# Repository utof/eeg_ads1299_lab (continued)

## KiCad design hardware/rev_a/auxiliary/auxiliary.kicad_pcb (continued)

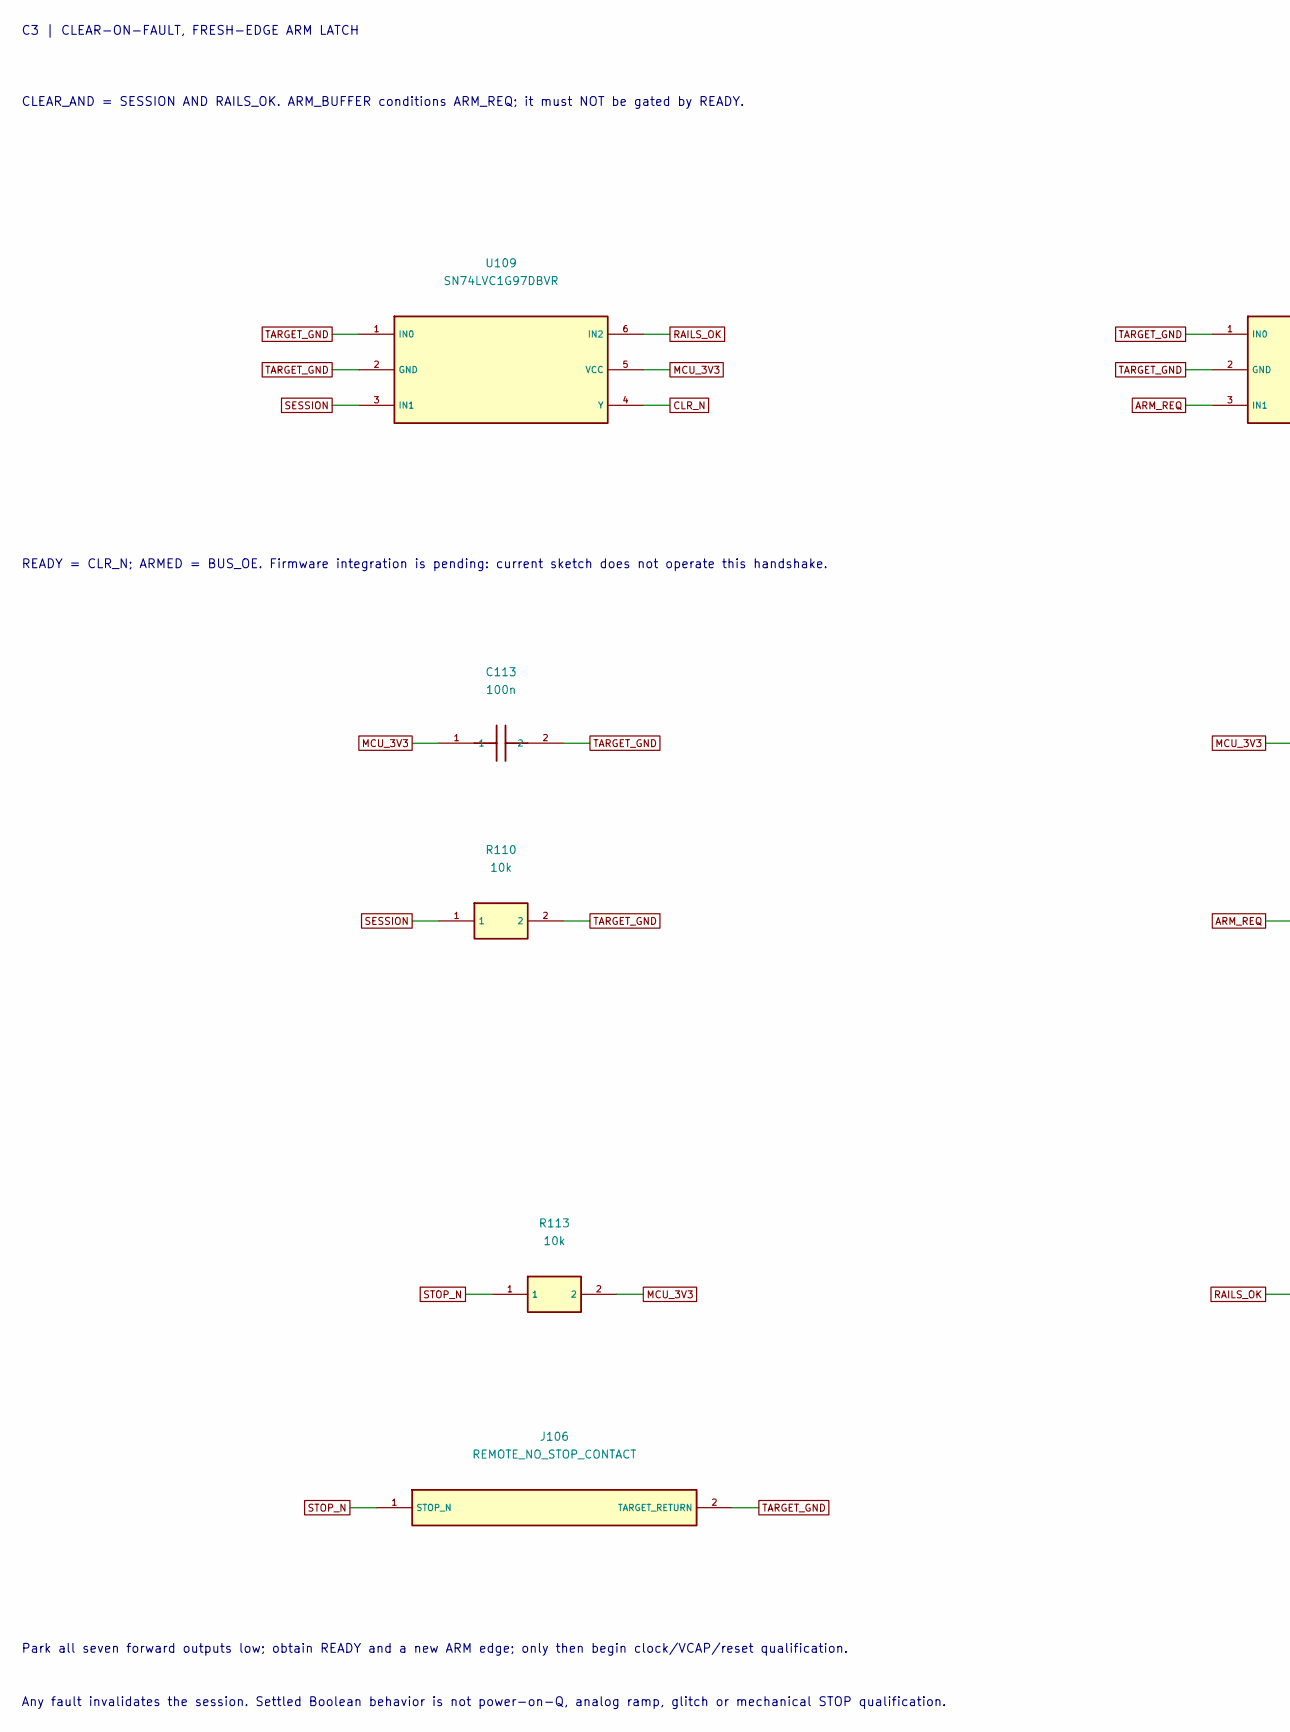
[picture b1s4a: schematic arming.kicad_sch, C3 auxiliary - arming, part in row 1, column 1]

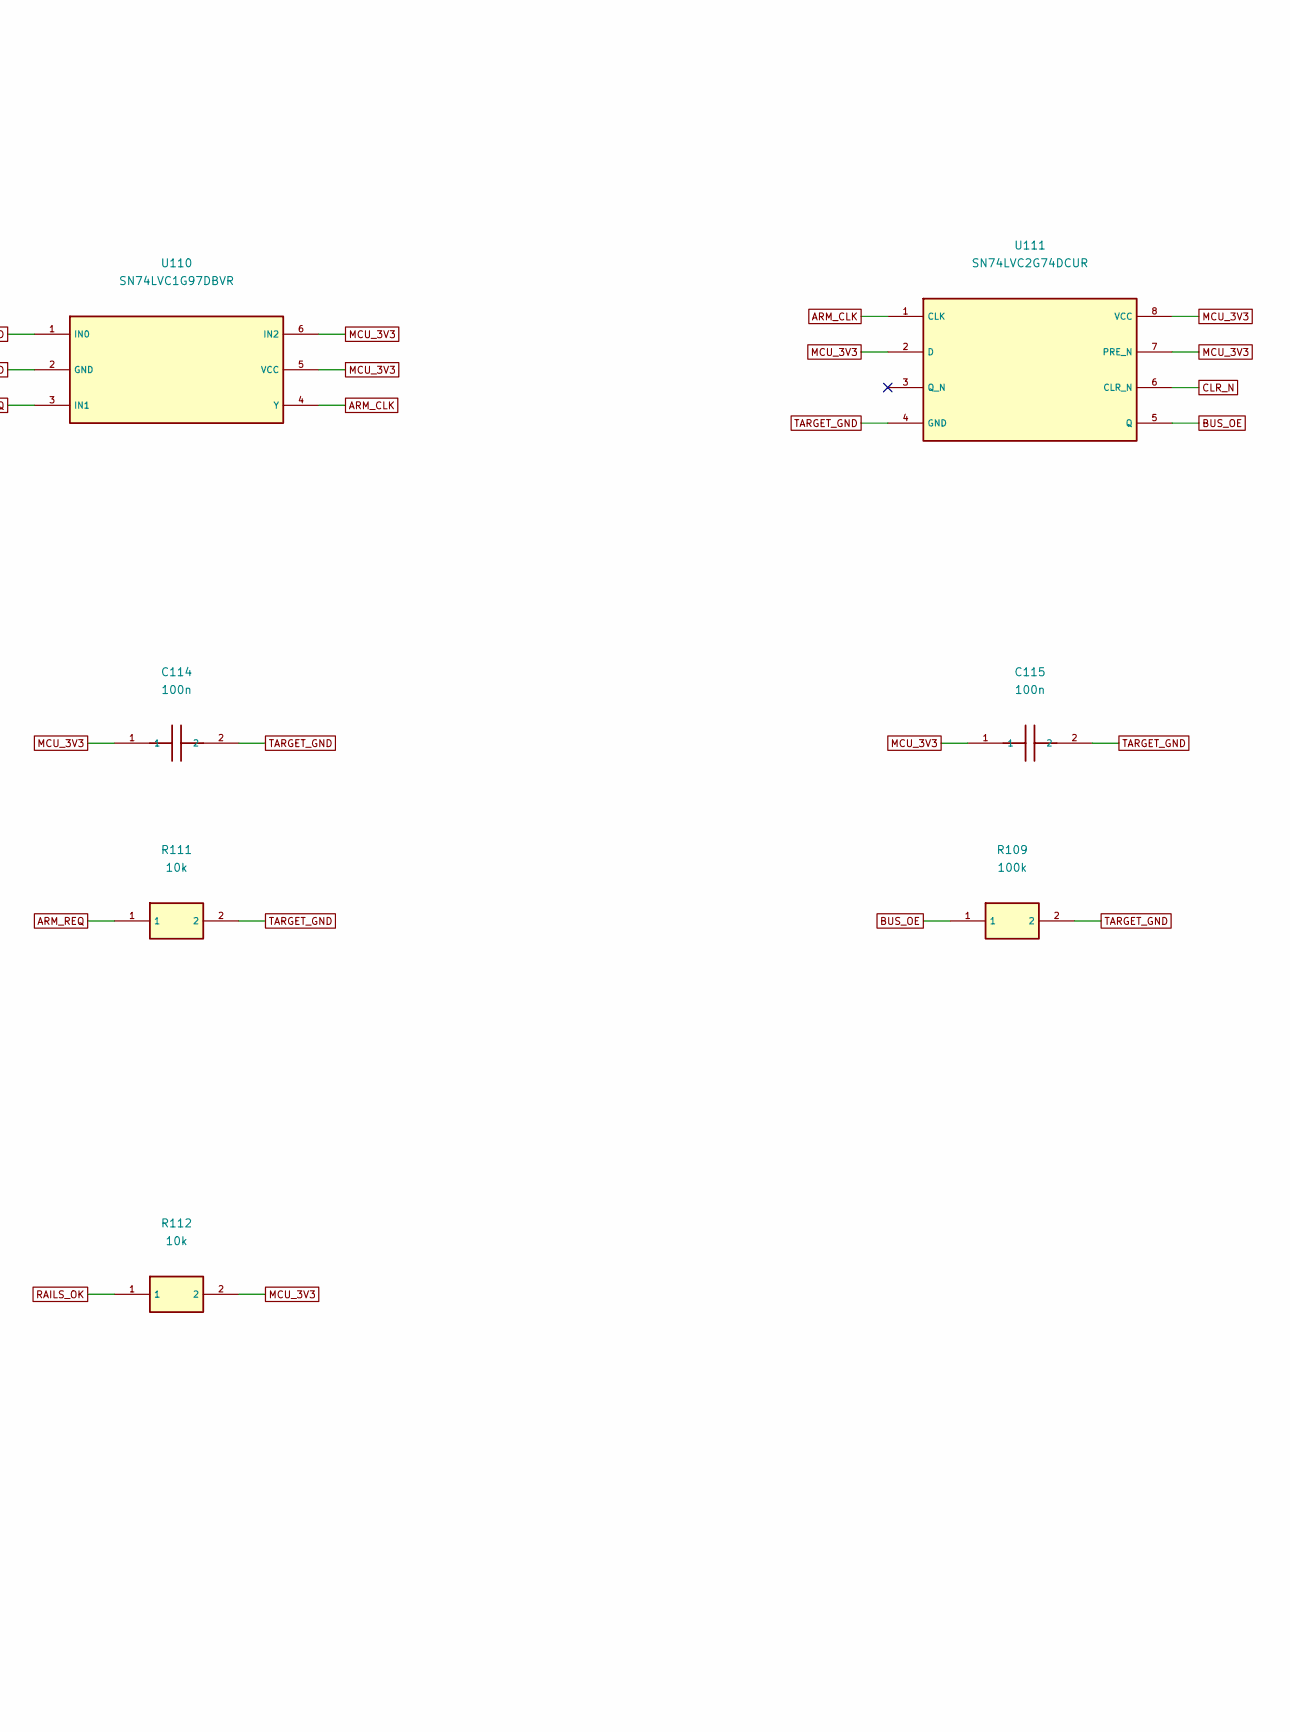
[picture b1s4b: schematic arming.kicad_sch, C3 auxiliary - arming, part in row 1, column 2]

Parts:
C113, C114, C115: 100n; C_0603_1608Metric; MPN C0603C104K5RACTU
J106: REMOTE_NO_STOP_CONTACT; SolderTails_2; MPN PCB_LANDINGS_ONLY
R109: 100k; R_0603_1608Metric; MPN RC0603FR-07100KL
R110, R111, R112, R113: 10k; R_0603_1608Metric; MPN RC0603FR-0710KL
U109, U110: SN74LVC1G97DBVR; SOT-23-6; MPN SN74LVC1G97DBVR
U111: SN74LVC2G74DCUR; VSSOP-8_2.3x2mm_P0.5mm; MPN SN74LVC2G74DCUR

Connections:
ARM_CLK: U110.4 (Y), U111.1 (CLK)
ARM_REQ: R111.1, U110.3 (IN1); also elsewhere on the board
BUS_OE: R109.1, U111.5 (Q); also elsewhere on the board
CLR_N: U109.4 (Y), U111.6 (CLR_N); also elsewhere on the board
MCU_3V3: C113.1, C114.1, C115.1, R112.2, R113.2, U109.5 (VCC), U110.5 (VCC), U110.6 (IN2), U111.2 (D), U111.7 (PRE_N), U111.8 (VCC); also elsewhere on the board
RAILS_OK: R112.1, U109.6 (IN2); also elsewhere on the board
SESSION: R110.1, U109.3 (IN1); also elsewhere on the board
STOP_N: J106.1 (STOP_N), R113.1; also elsewhere on the board
TARGET_GND: C113.2, C114.2, C115.2, J106.2 (TARGET_RETURN), R109.2, R110.2, R111.2, U109.1 (IN0), U109.2 (GND), U110.1 (IN0), U110.2 (GND), U111.4 (GND); also elsewhere on the board

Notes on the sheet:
C3 | CLEAR-ON-FAULT, FRESH-EDGE ARM LATCH
CLEAR_AND = SESSION AND RAILS_OK. ARM_BUFFER conditions ARM_REQ; it must NOT be gated by READY.
READY = CLR_N; ARMED = BUS_OE. Firmware integration is pending: current sketch does not operate this handshake.
Park all seven forward outputs low; obtain READY and a new ARM edge; only then begin clock/VCAP/reset qualification.
Any fault invalidates the session. Settled Boolean behavior is not power-on-Q, analog ramp, glitch or mechanical STOP qualification.

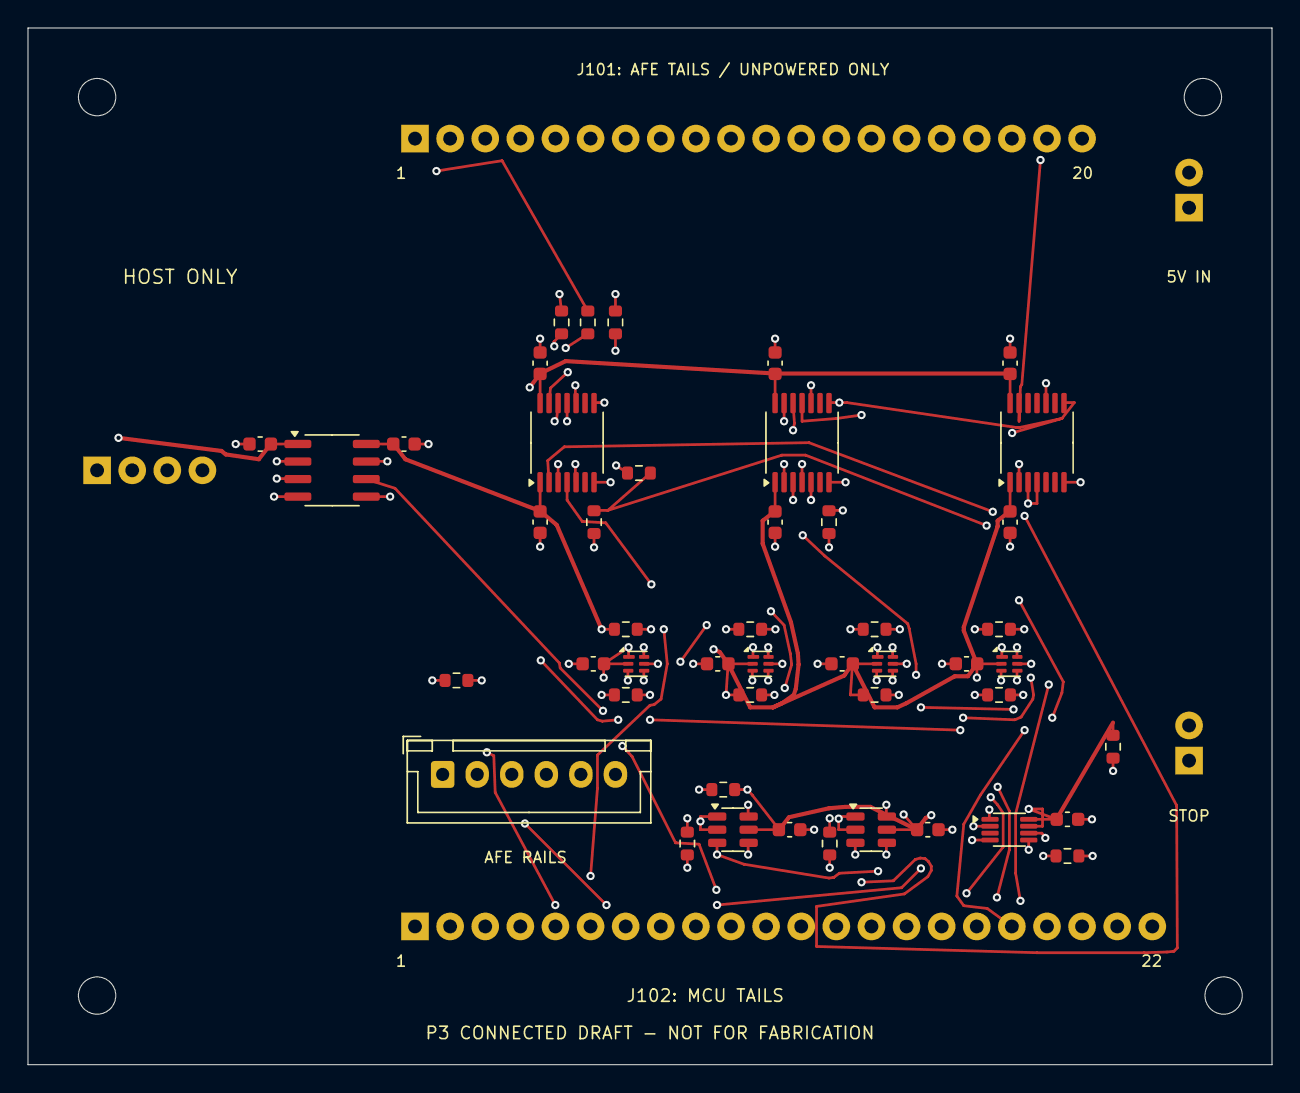
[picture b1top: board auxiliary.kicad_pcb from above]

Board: 4 copper layers, 90.0 x 75.0 mm, 56 parts (0 on the bottom side), 45 nets.

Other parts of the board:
H1, H2, H3, H4: M2.5_CLEARANCE_ONLY; MountingHole_2.7mm_M2.5

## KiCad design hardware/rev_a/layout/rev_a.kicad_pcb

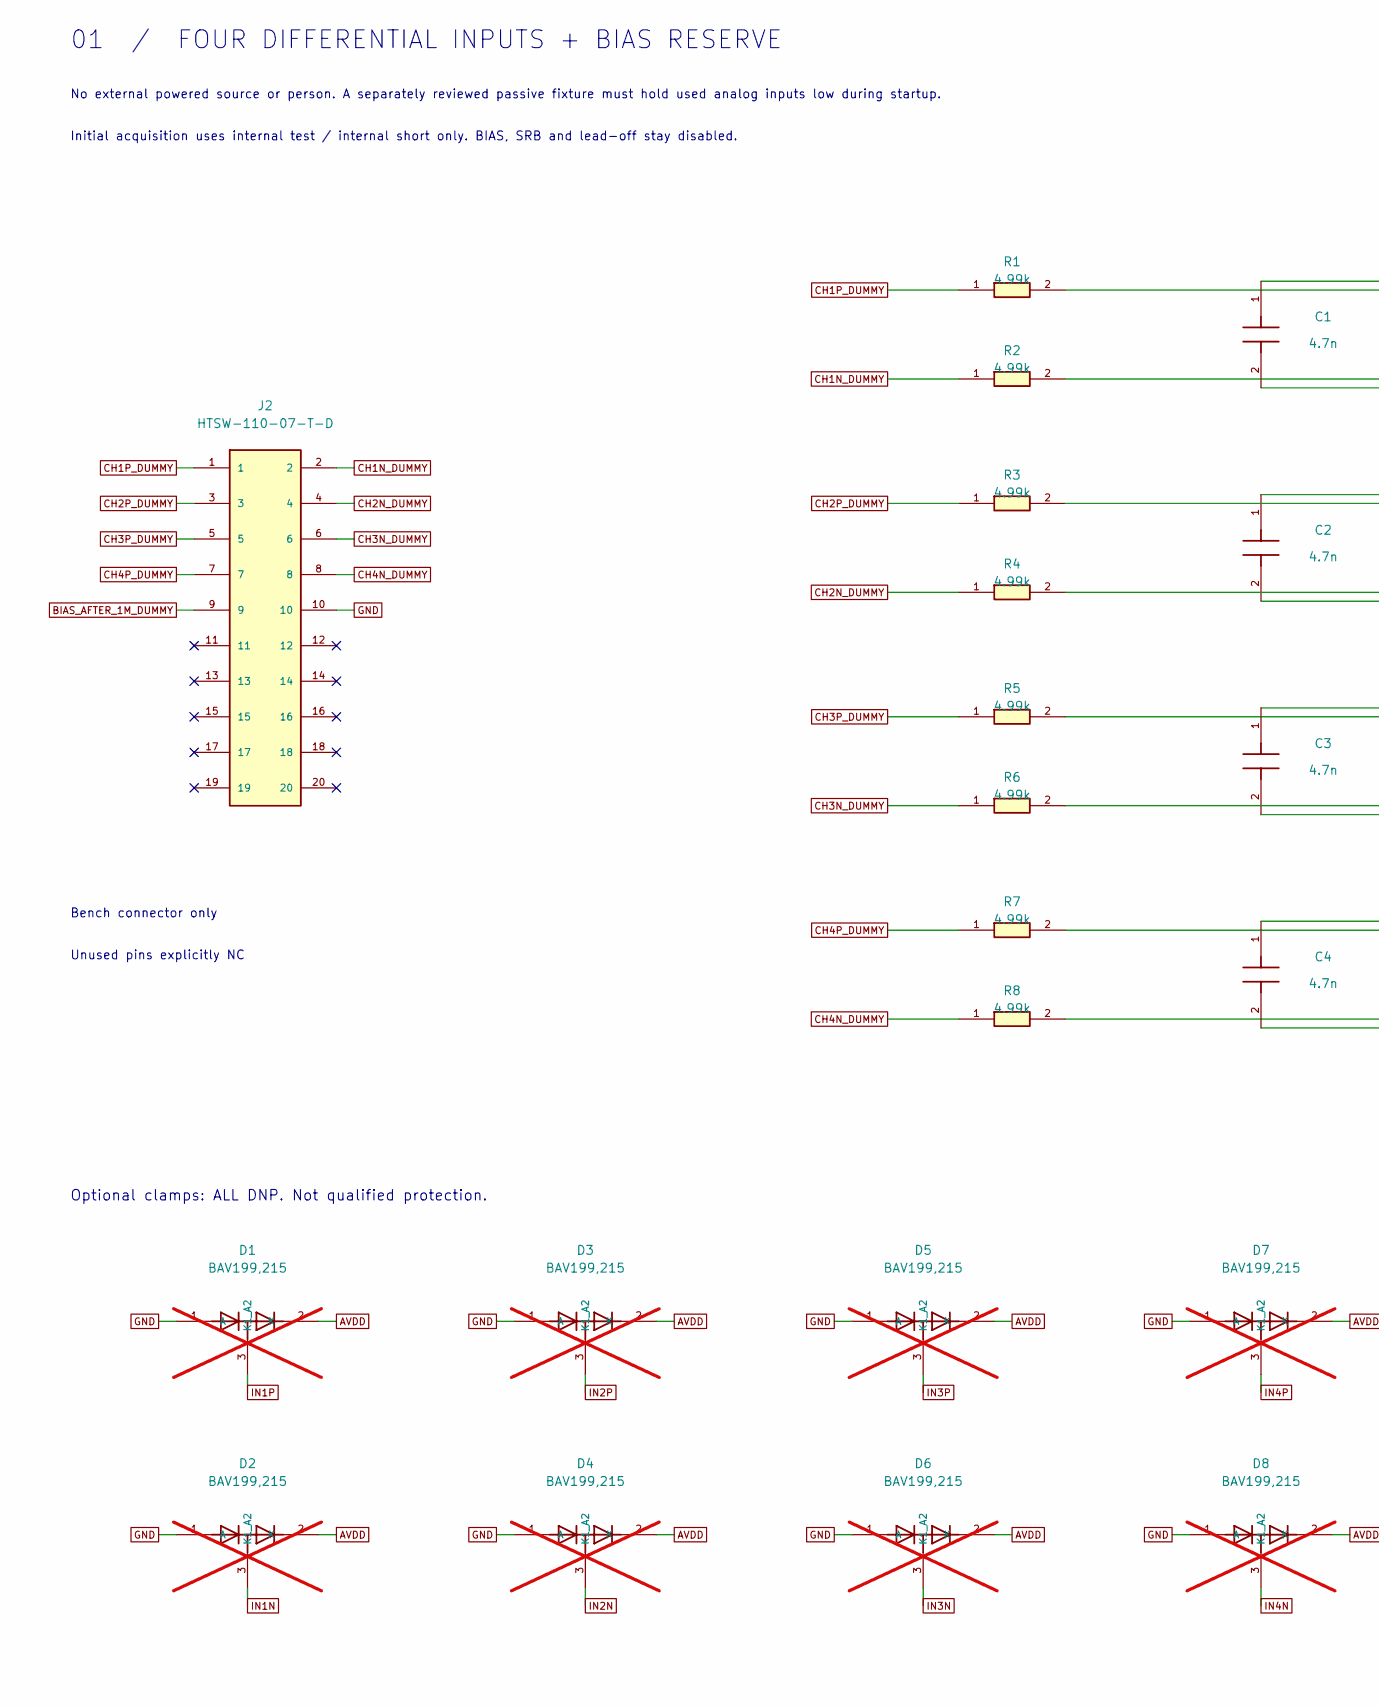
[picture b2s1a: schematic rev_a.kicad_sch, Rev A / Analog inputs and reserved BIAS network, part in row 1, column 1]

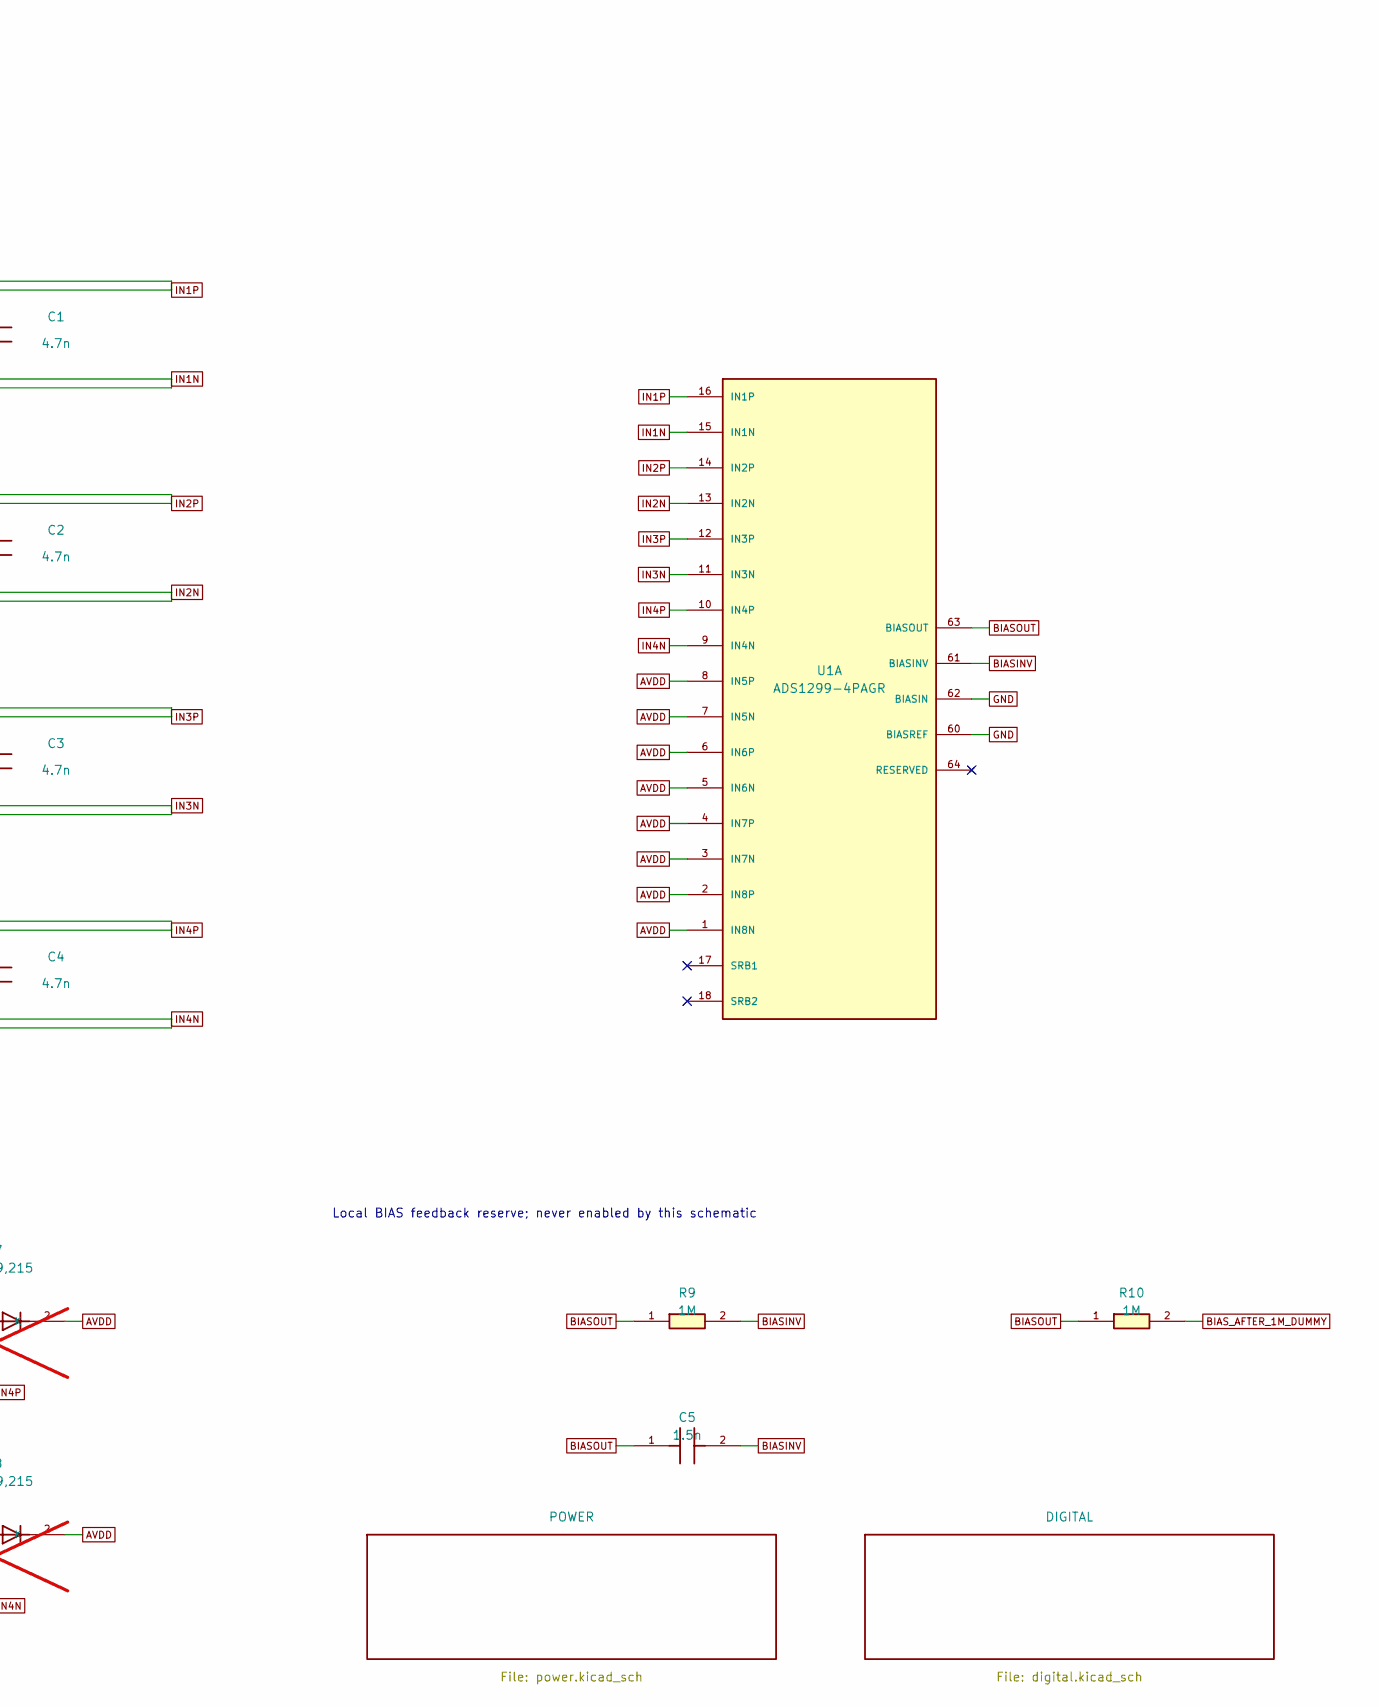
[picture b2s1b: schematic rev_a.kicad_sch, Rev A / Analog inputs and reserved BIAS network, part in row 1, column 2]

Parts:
C1, C2, C3, C4: 4.7n; C_0603_1608Metric; Tolerance 0.05; MPN GRM1885C1H472JA01D
C5: 1.5n; C_0603_1608Metric; Tolerance 0.05; MPN GRM1885C1H152JA01D
D1, D2, D3, D4, D5, D6, D7, D8: BAV199,215; SOT-23; MPN BAV199,215; not fitted
J2: HTSW-110-07-T-D; PinHeader_2x10_P2.54mm_Vertical; MPN HTSW-110-07-T-D
R1, R2, R3, R4, R5, R6, R7, R8: 4.99k; R_0603_1608Metric; Tolerance 0.01; MPN RC0603FR-074K99L
R9, R10: 1M; R_0603_1608Metric; Tolerance 0.01; MPN RC0603FR-071ML
U1: ADS1299-4PAGR; TQFP-64_10x10mm_P0.5mm; MPN ADS1299-4PAGR

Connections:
AVDD: D1.2 (K), D2.2 (K), D3.2 (K), D4.2 (K), D5.2 (K), D6.2 (K), D7.2 (K), D8.2 (K), U1.1 (IN8N), U1.2 (IN8P), U1.3 (IN7N), U1.4 (IN7P), U1.5 (IN6N), U1.6 (IN6P), U1.7 (IN5N), U1.8 (IN5P); also elsewhere on the board
BIASINV: C5.2, R9.2, U1.61 (BIASINV)
BIASOUT: C5.1, R9.1, R10.1, U1.63 (BIASOUT)
BIAS_AFTER_1M_DUMMY: J2.9, R10.2
CH1N_DUMMY: J2.2, R2.1
CH1P_DUMMY: J2.1, R1.1
CH2N_DUMMY: J2.4, R4.1
CH2P_DUMMY: J2.3, R3.1
CH3N_DUMMY: J2.6, R6.1
CH3P_DUMMY: J2.5, R5.1
CH4N_DUMMY: J2.8, R8.1
CH4P_DUMMY: J2.7, R7.1
GND: D1.1 (A), D2.1 (A), D3.1 (A), D4.1 (A), D5.1 (A), D6.1 (A), D7.1 (A), D8.1 (A), J2.10, U1.60 (BIASREF), U1.62 (BIASIN); also elsewhere on the board
IN1N: C1.2, D2.3 (K1_A2), R2.2, U1.15 (IN1N)
IN1P: C1.1, D1.3 (K1_A2), R1.2, U1.16 (IN1P)
IN2N: C2.2, D4.3 (K1_A2), R4.2, U1.13 (IN2N)
IN2P: C2.1, D3.3 (K1_A2), R3.2, U1.14 (IN2P)
IN3N: C3.2, D6.3 (K1_A2), R6.2, U1.11 (IN3N)
IN3P: C3.1, D5.3 (K1_A2), R5.2, U1.12 (IN3P)
IN4N: C4.2, D8.3 (K1_A2), R8.2, U1.9 (IN4N)
IN4P: C4.1, D7.3 (K1_A2), R7.2, U1.10 (IN4P)

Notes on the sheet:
01 / FOUR DIFFERENTIAL INPUTS + BIAS RESERVE
No external powered source or person. A separately reviewed passive fixture must hold used analog inputs low during startup.
Initial acquisition uses internal test / internal short only. BIAS, SRB and lead-off stay disabled.
Bench connector only
Unused pins explicitly NC
Local BIAS feedback reserve; never enabled by this schematic
Optional clamps: ALL DNP. Not qualified protection.

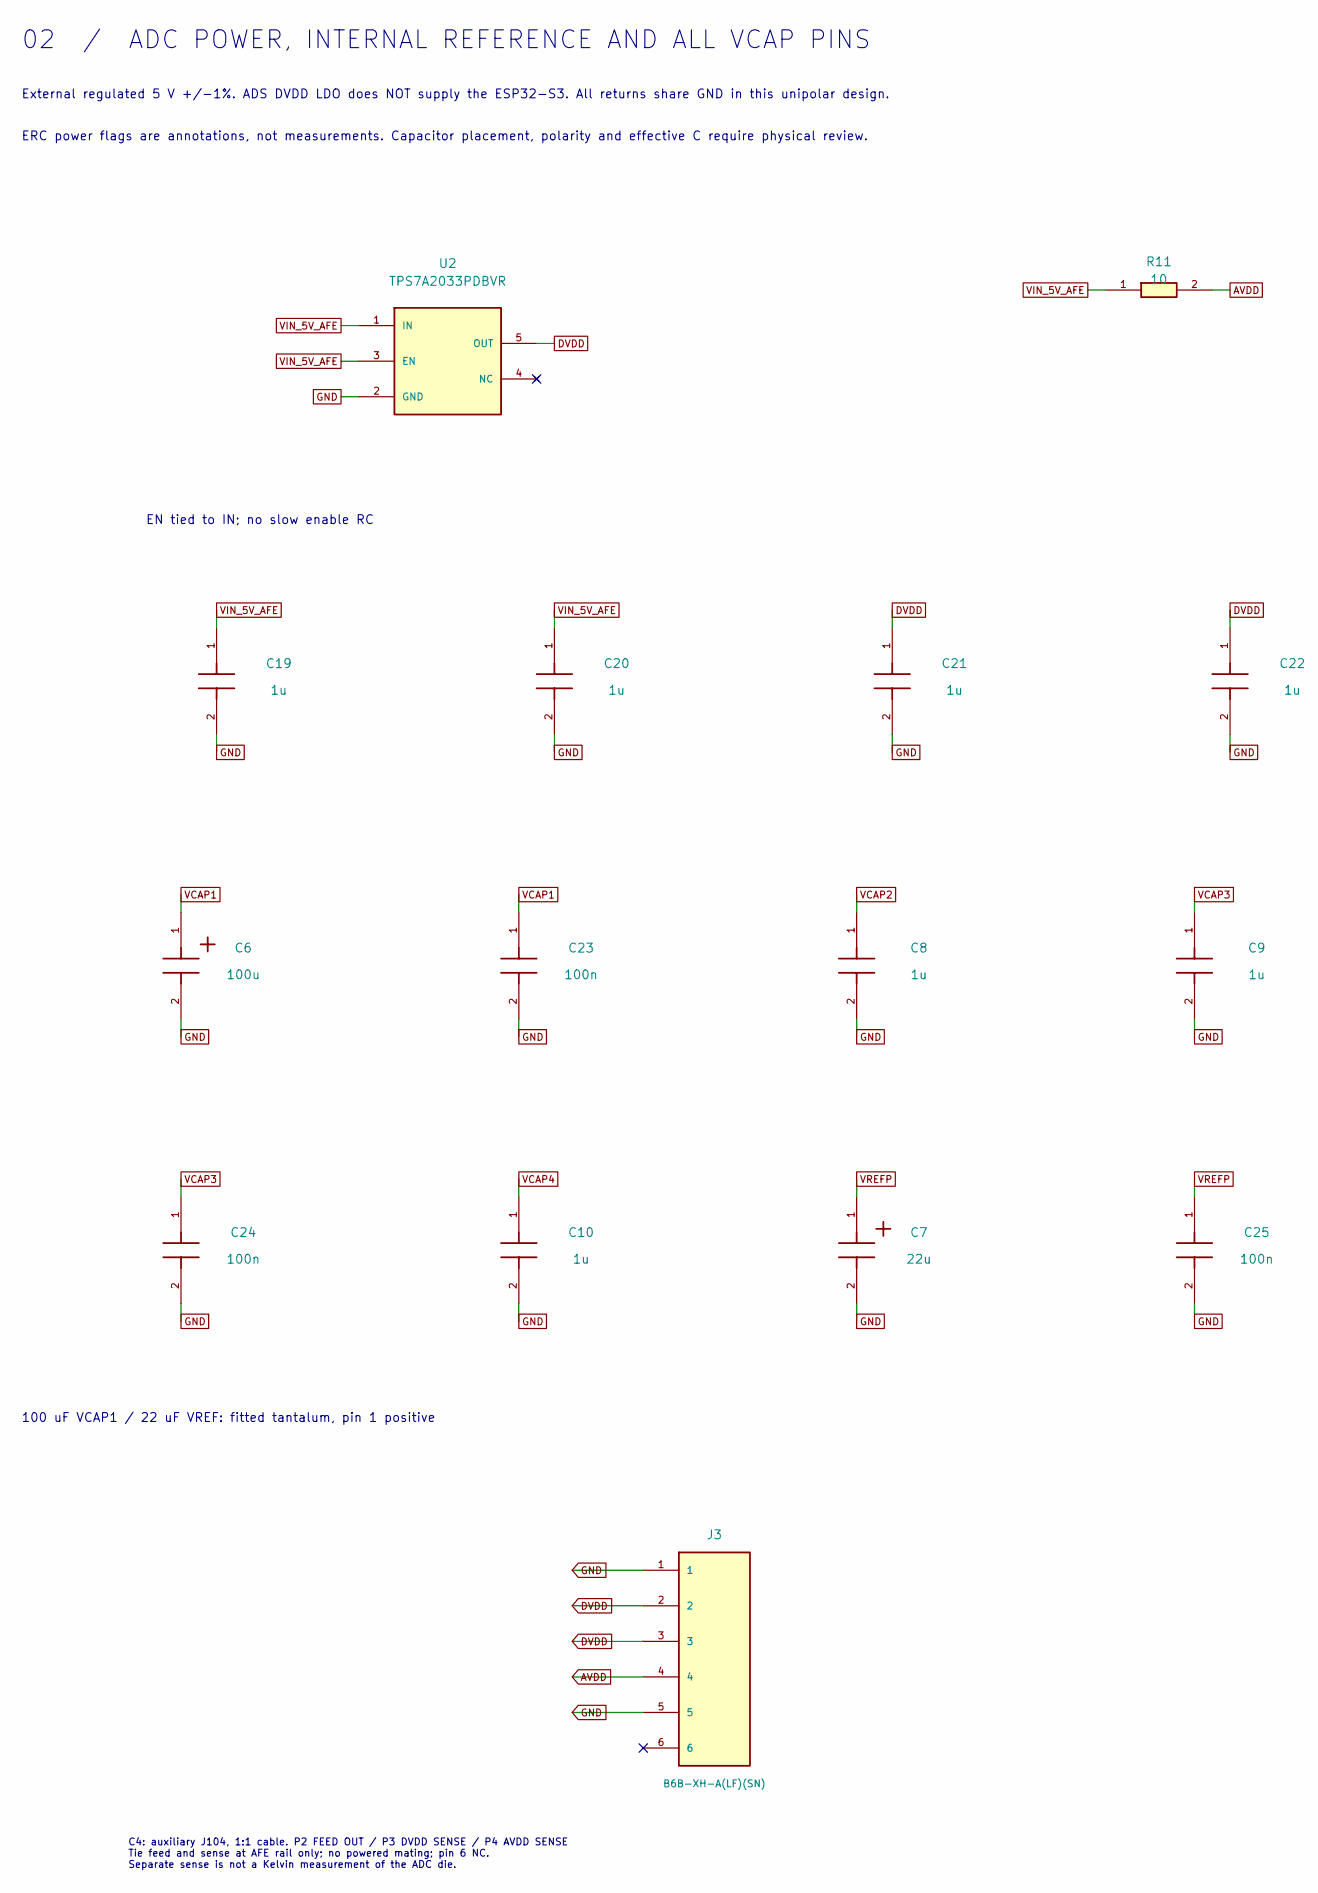
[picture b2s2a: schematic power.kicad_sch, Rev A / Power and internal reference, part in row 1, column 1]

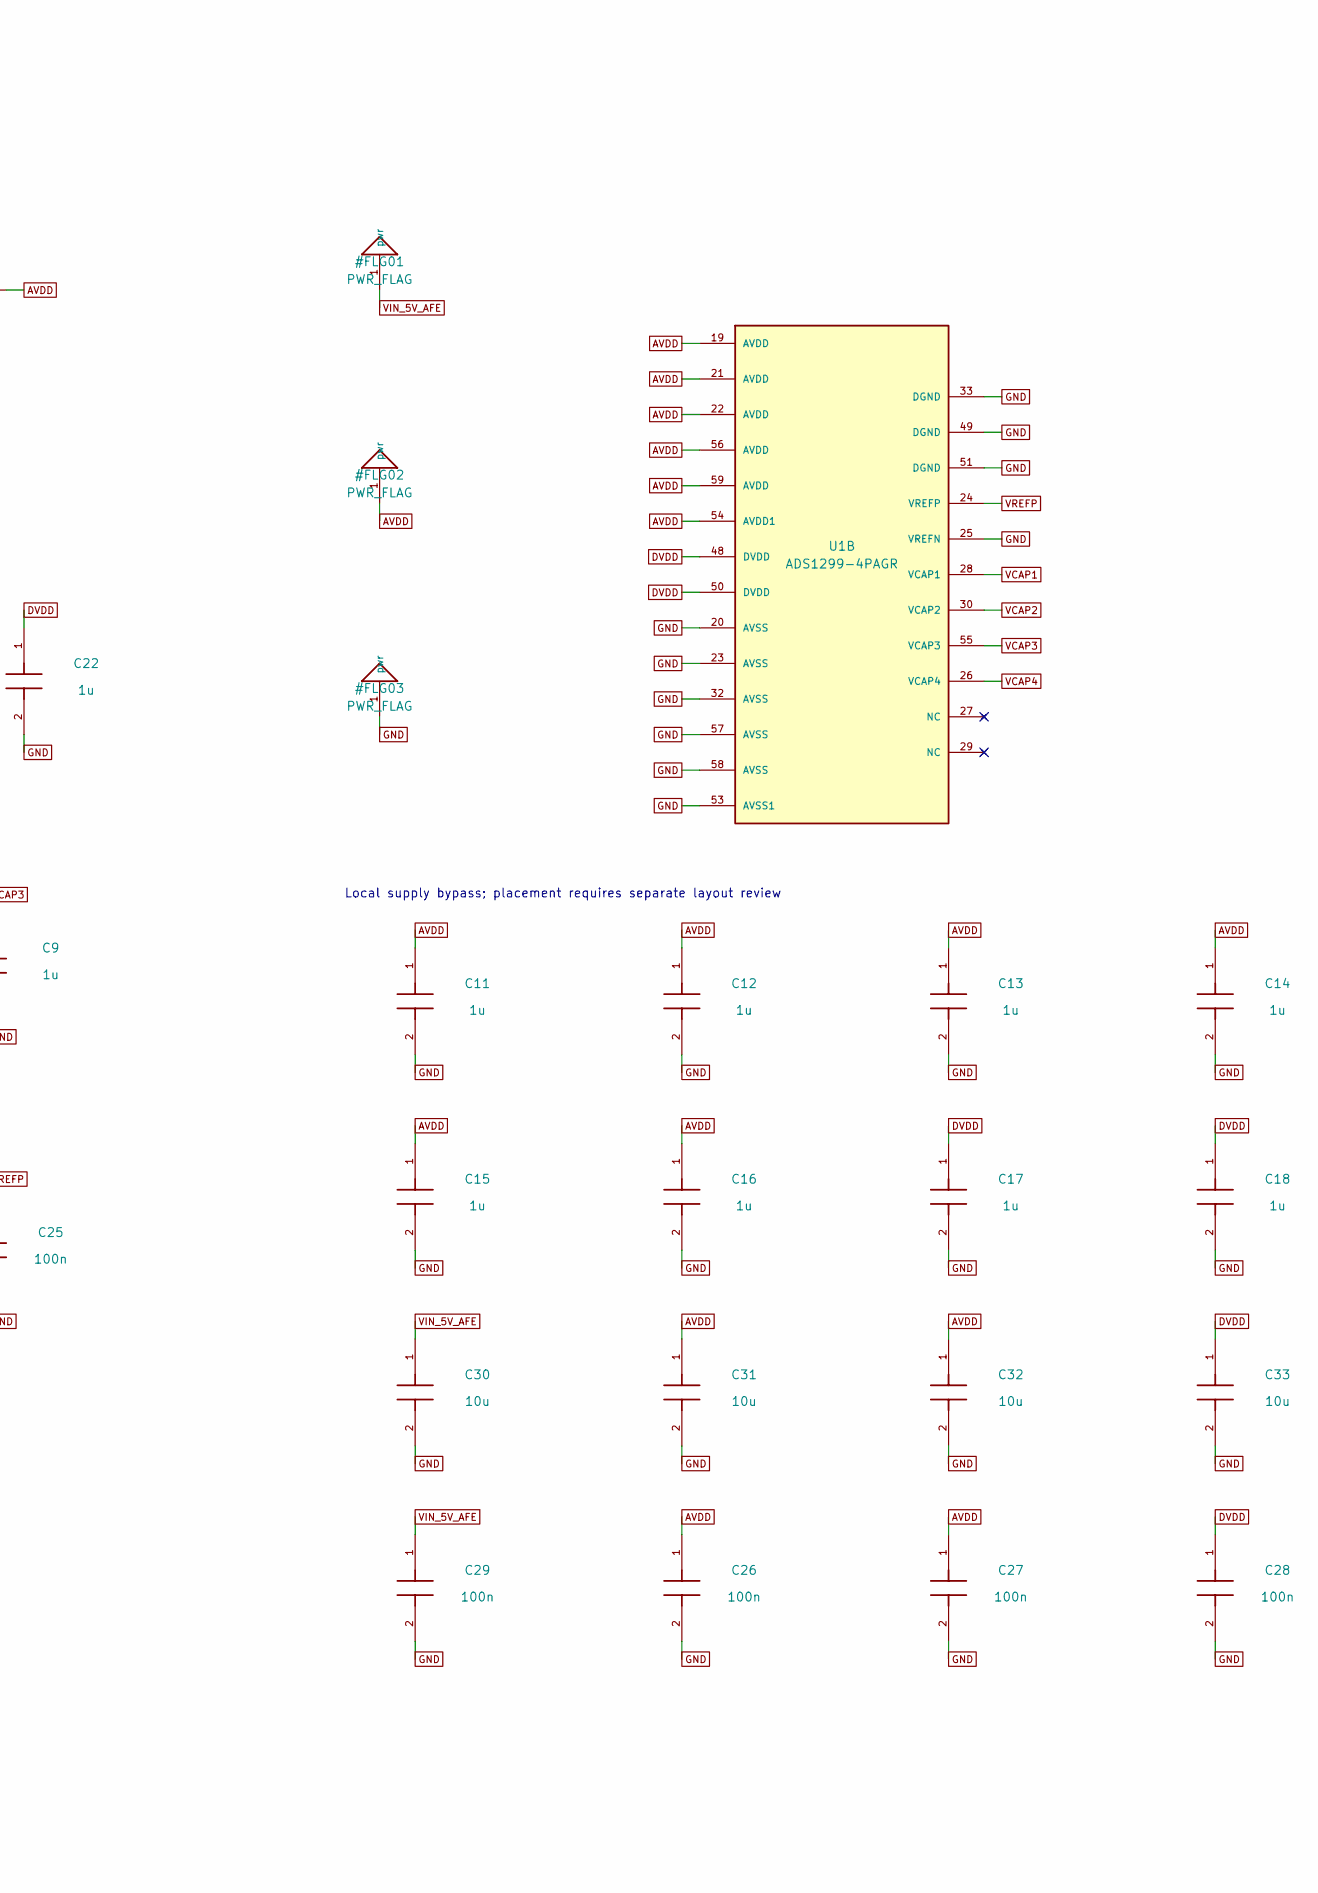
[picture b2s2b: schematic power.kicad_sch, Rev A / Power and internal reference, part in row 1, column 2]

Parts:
C6: 100u; T491D_7343_DensityB; Tolerance 0.1; MPN T491D107K016AT
C7: 22u; T491B_3528_DensityB; Tolerance 0.1; MPN T491B226K016AT
C8, C9, C10, C11, C12, C13, C14, C15, C16, C17, C18, C19, C20, C21, C22: 1u; C_0603_1608Metric; Tolerance 0.1; MPN GRM188R61E105KA12D
C23, C24, C25, C26, C27, C28, C29: 100n; C_0603_1608Metric; Tolerance 0.1; MPN GRM188R71H104KA93D
C30, C31, C32, C33: 10u; C_0805_2012Metric; Tolerance 0.1; MPN GRM219R61A106KE44D
J3: B6B-XH-A(LF)(SN); JST_XH_B6B-XH-A_1x06_P2.50mm_Vertical; MPN B6B-XH-A(LF)(SN)
R11: 10; R_0603_1608Metric; Tolerance 0.01; MPN RC0603FR-0710RL
U1: ADS1299-4PAGR; TQFP-64_10x10mm_P0.5mm; MPN ADS1299-4PAGR
U2: TPS7A2033PDBVR; SOT-23-5; MPN TPS7A2033PDBVR

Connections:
AVDD: C11.1, C12.1, C13.1, C14.1, C15.1, C16.1, C26.1, C27.1, C31.1, C32.1, J3.4, R11.2, U1.19 (AVDD), U1.21 (AVDD), U1.22 (AVDD), U1.54 (AVDD1), U1.56 (AVDD), U1.59 (AVDD); also elsewhere on the board
DVDD: C17.1, C18.1, C21.1, C22.1, C28.1, C33.1, J3.2, J3.3, U1.48 (DVDD), U1.50 (DVDD), U2.5 (OUT)
GND: C6.2, C7.2, C8.2, C9.2, C10.2, C11.2, C12.2, C13.2, C14.2, C15.2, C16.2, C17.2, C18.2, C19.2, C20.2, C21.2, C22.2, C23.2, C24.2, C25.2, C26.2, C27.2, C28.2, C29.2, C30.2, C31.2, C32.2, C33.2, J3.1, J3.5, U1.20 (AVSS), U1.23 (AVSS), U1.25 (VREFN), U1.32 (AVSS), U1.33 (DGND), U1.49 (DGND), U1.51 (DGND), U1.53 (AVSS1), U1.57 (AVSS), U1.58 (AVSS), U2.2 (GND); also elsewhere on the board
VCAP1: C6.1, C23.1, U1.28 (VCAP1)
VCAP2: C8.1, U1.30 (VCAP2)
VCAP3: C9.1, C24.1, U1.55 (VCAP3)
VCAP4: C10.1, U1.26 (VCAP4)
VIN_5V_AFE: C19.1, C20.1, C29.1, C30.1, R11.1, U2.1 (IN), U2.3 (EN); also elsewhere on the board
VREFP: C7.1, C25.1, U1.24 (VREFP)

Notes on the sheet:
02 / ADC POWER, INTERNAL REFERENCE AND ALL VCAP PINS
External regulated 5 V +/-1%. ADS DVDD LDO does NOT supply the ESP32-S3. All returns share GND in this unipolar design.
ERC power flags are annotations, not measurements. Capacitor placement, polarity and effective C require physical review.
EN tied to IN; no slow enable RC
100 uF VCAP1 / 22 uF VREF: fitted tantalum, pin 1 positive
Local supply bypass; placement requires separate layout review
C4: auxiliary J104, 1:1 cable. P2 FEED OUT / P3 DVDD SENSE / P4 AVDD SENSE Tie feed and sense at AFE rail only; no powered mating; pin 6 NC. Separate sense is not a Kelvin measurement of the ADC die.
